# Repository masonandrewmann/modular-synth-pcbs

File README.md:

A collection of PCBs I've designed since getting into DIY modular synths. Do not assume that any of these designs work or are good, many of them have errors I have not fixed yet. If you want to get some manufactured, go ahead but I'd urge you to contact me first and I can let you know any quirks of the board first! :~)

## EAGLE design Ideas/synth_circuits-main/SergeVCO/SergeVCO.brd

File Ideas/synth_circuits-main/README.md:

# synth_circuits
synthesizer circuits

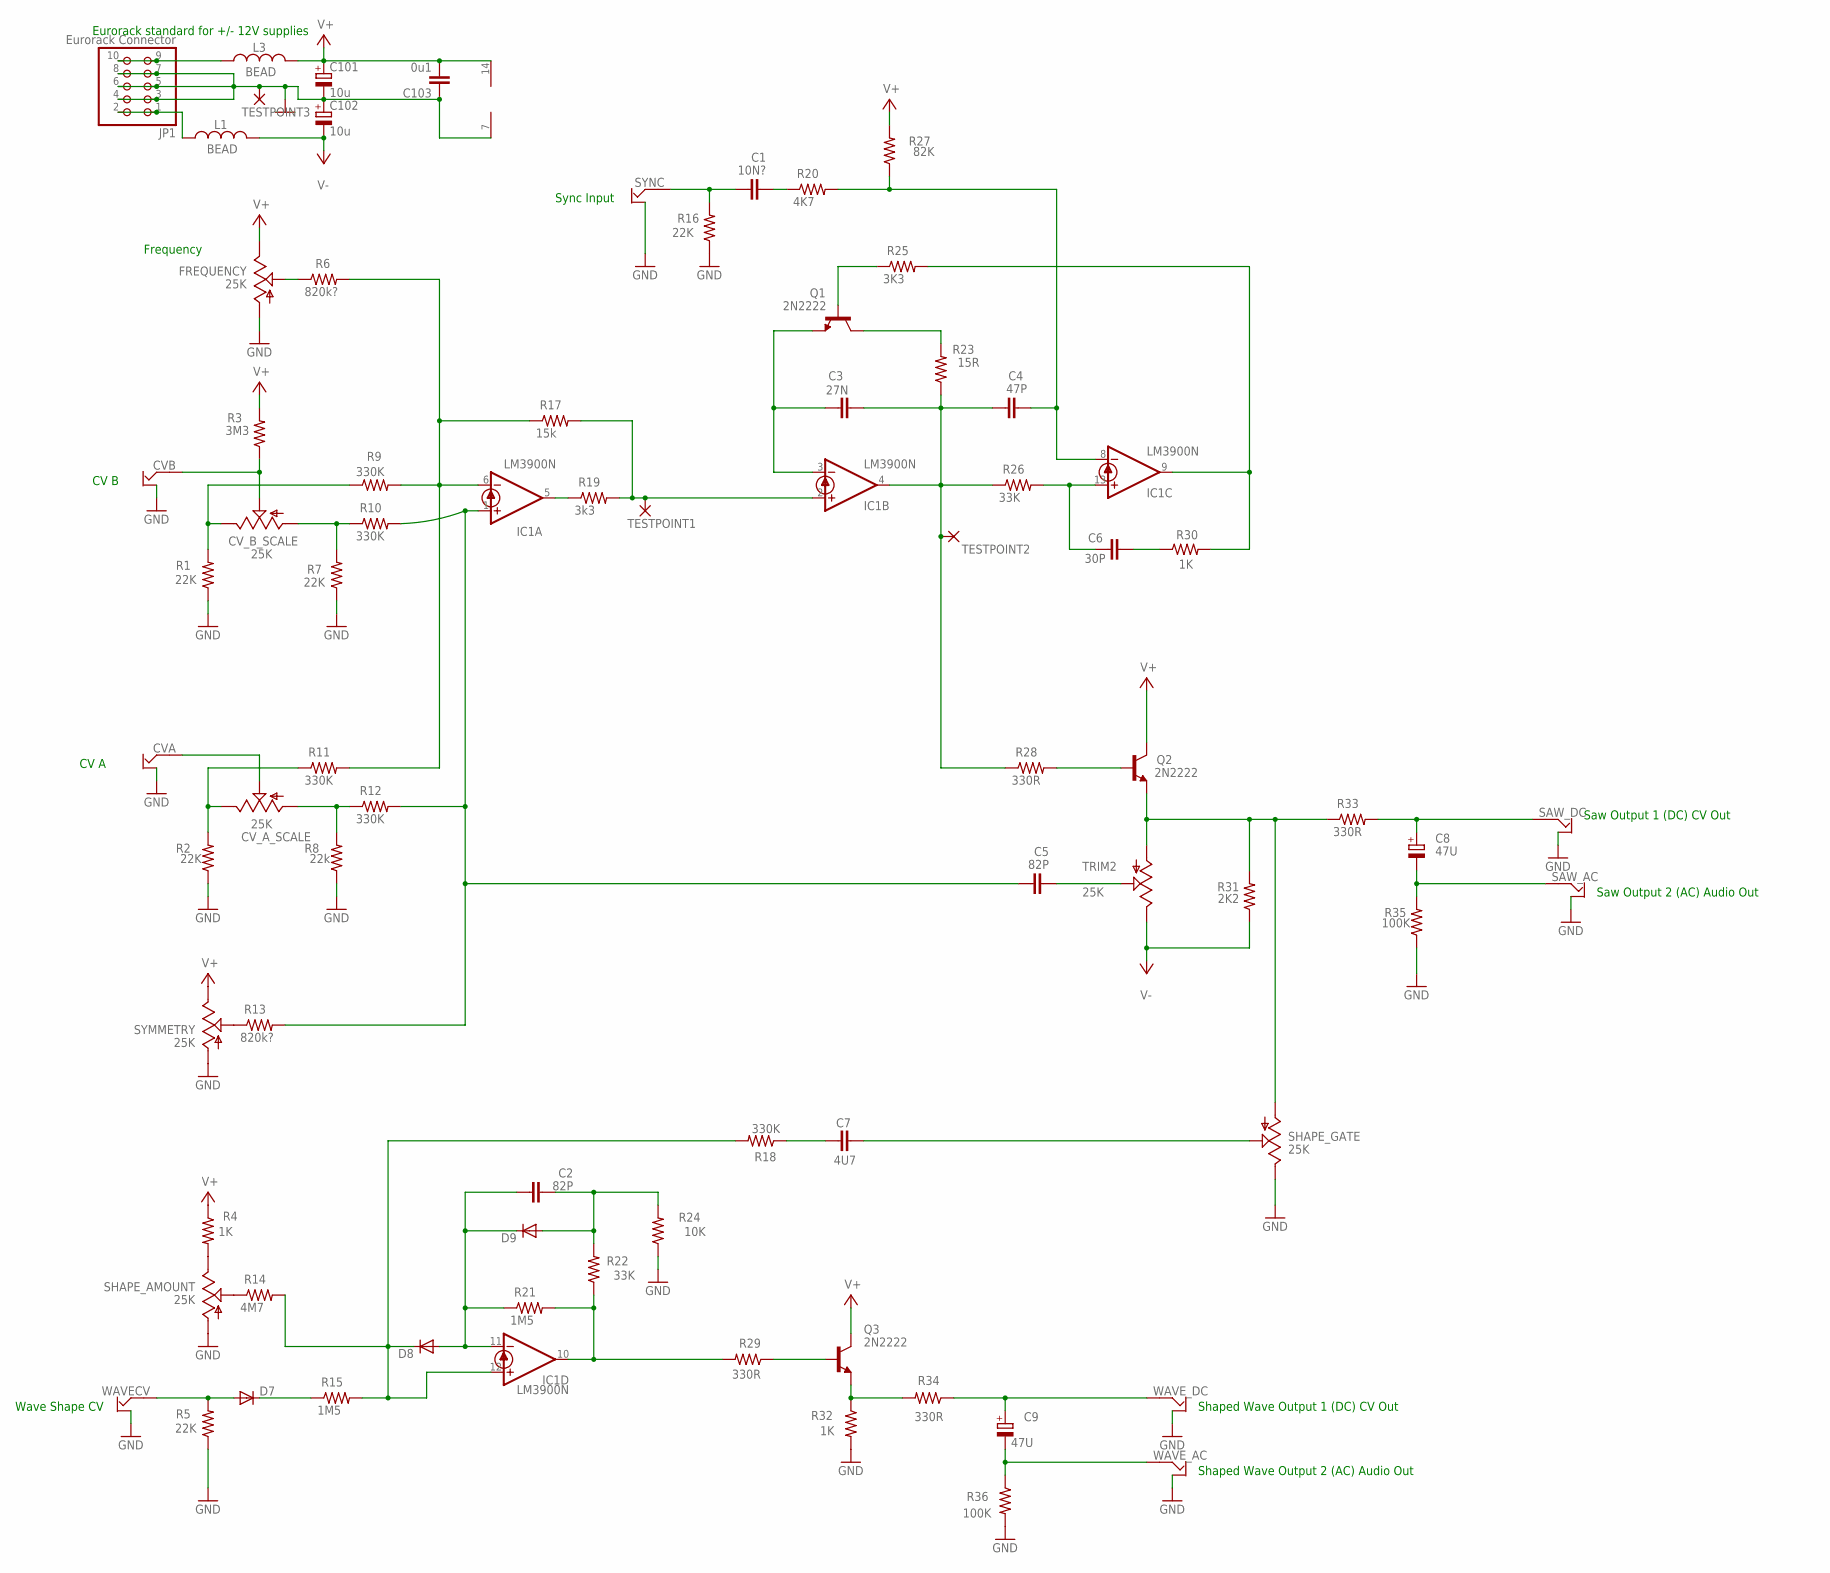
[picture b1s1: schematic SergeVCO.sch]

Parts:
C1: 10N?; C050-025X075-AARON
C2, C5: 82P; C050-025X075-AARON
C3: 27N; C050-025X075-AARON
C4: 47P; C050-025X075-AARON
C6: 30P; C050-025X075-AARON
C7: 4U7; C050-025X075-AARON
C8, C9: 47U; E1,8-4
C101, C102: 10u; E1,8-4
C103: 0u1; C050-025X075-AARON
CVA: OFFBOARD2JACKALT_AARON; OFFBOARD2JACKALT
CVB: OFFBOARD2JACKALT_AARON; OFFBOARD2JACKALT
CV_A_SCALE: 25K; B64Y
CV_B_SCALE: 25K; B64Y
D7, D8, D9: SMALL_DIODEDO35-7; DO35-7
FREQUENCY: 25K; B64Y
IC1: LM3900N; DIL14
JP1: Eurorack Connector; 2X05
L1, L3: BEAD; 0207/10
Q1, Q2, Q3: 2N2222; TO92-EBC-OVAL
R1, R2, R5, R7, R16: 22K; 0207/10
R3: 3M3; 0207/10
R4, R30, R32: 1K; 0207/10
R6, R13: 820k?; 0207/10
R8: 22k; 0207/10
R9, R10, R11, R12, R18: 330K; 0207/10
R14: 4M7; 0207/10
R15, R21: 1M5; 0207/10
R17: 15k; 0207/10
R19: 3k3; 0207/10
R20: 4K7; 0207/10
R22, R26: 33K; 0207/10
R23: 15R; 0207/10
R24: 10K; 0207/10
R25: 3K3; 0207/10
R27: 82K; 0207/10
R28, R29, R33, R34: 330R; 0207/10
R31: 2K2; 0207/10
R35, R36: 100K; 0207/10
SAW_AC: OFFBOARD2JACKALT_AARON; OFFBOARD2JACKALT
SAW_DC: OFFBOARD2JACKALT_AARON; OFFBOARD2JACKALT
SHAPE_AMOUNT: 25K; B64Y
SHAPE_GATE: 25K; B64Y
SYMMETRY: 25K; B64Y
SYNC: OFFBOARD2JACKALT_AARON; OFFBOARD2JACKALT
TESTPOINT1, TESTPOINT2, TESTPOINT3: IOPAD_AARON; ELLIPTICALPADSINGLE
TRIM2: 25K; RS3
WAVECV: OFFBOARD2JACKALT_AARON; OFFBOARD2JACKALT
WAVE_AC: OFFBOARD2JACKALT_AARON; OFFBOARD2JACKALT
WAVE_DC: OFFBOARD2JACKALT_AARON; OFFBOARD2JACKALT

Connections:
GND: C101.-, C102.+, C103.1, CVA.GND, CVB.GND, FREQUENCY.A, IC1.7 (GND), JP1.3, JP1.4, JP1.5, JP1.6, JP1.7, JP1.8, R1.1, R2.1, R5.1, R7.1, R8.1, R16.1, R24.1, R32.2, R35.1, R36.2, SAW_AC.GND, SAW_DC.GND, SHAPE_AMOUNT.A, SHAPE_GATE.E, SYMMETRY.A, SYNC.GND, TESTPOINT3.P$1, WAVECV.GND, WAVE_AC.GND, WAVE_DC.GND
unnamed: FREQUENCY.S, R6.1
unnamed: CVB.SIGNAL, CV_B_SCALE.S, R3.1
unnamed: CV_B_SCALE.E, R1.2, R9.1
unnamed: CV_B_SCALE.A, R7.2, R10.1
unnamed: R13.1, SYMMETRY.S
unnamed: R4.2, SHAPE_AMOUNT.E
unnamed: R14.1, SHAPE_AMOUNT.S
unnamed: D7.A, R5.2, WAVECV.SIGNAL
unnamed: D7.C, R15.1
unnamed: CVA.SIGNAL, CV_A_SCALE.S
unnamed: CV_A_SCALE.E, R2.2, R11.1
unnamed: CV_A_SCALE.A, R8.2, R12.1
unnamed: C5.1, IC1.1 (+IN), R10.2, R12.2, R13.2
unnamed: IC1.6 (-IN), R6.2, R9.2, R11.2, R17.1
unnamed: C3.1, IC1.3 (-IN), Q1.E
unnamed: C2.1, D8.A, D9.C, IC1.11 (-IN), R21.1
unnamed: D8.C, IC1.12 (+IN), R14.2, R15.2, R18.2
unnamed: IC1.10 (OUT), R21.2, R22.1, R29.2
unnamed: C2.2, D9.A, R22.2, R24.2
unnamed: C7.1, R18.1
unnamed: C7.2, SHAPE_GATE.S
unnamed: Q3.B, R29.1
unnamed: Q3.E, R32.1, R34.2
unnamed: C9.-, R36.1, WAVE_AC.SIGNAL
unnamed: C9.+, R34.1, WAVE_DC.SIGNAL
unnamed: IC1.2 (+IN), R17.2, R19.2, TESTPOINT1.P$1
unnamed: IC1.5 (OUT), R19.1
unnamed: C1.1, R16.2, SYNC.SIGNAL
unnamed: C3.2, C4.1, IC1.4 (OUT), R23.1, R26.1, R28.1, TESTPOINT2.P$1
unnamed: C1.2, R20.1
unnamed: Q1.C, R23.2
unnamed: Q1.B, R25.1
unnamed: C6.1, IC1.13 (+IN), R26.2
unnamed: Q2.B, R28.2
unnamed: C4.2, IC1.8 (-IN), R20.2, R27.1
unnamed: C6.2, R30.1
unnamed: IC1.9 (OUT), R25.2, R30.2
unnamed: C8.+, R33.2, SAW_DC.SIGNAL
unnamed: Q2.E, R31.2, R33.1, SHAPE_GATE.A, TRIM2.A
unnamed: C5.2, TRIM2.S
unnamed: C8.-, R35.2, SAW_AC.SIGNAL
unnamed: JP1.1, JP1.2, L1.1
unnamed: JP1.9, JP1.10, L3.1
V+: C101.+, C103.2, FREQUENCY.E, IC1.14 (V+), L3.2, Q2.C, Q3.C, R3.2, R4.1, R27.2, SYMMETRY.E
V-: C102.-, L1.2, R31.1, TRIM2.E

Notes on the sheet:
Eurorack standard for +/- 12V supplies
Frequency
CV B
CV A
Shaped Wave Output 1 (DC) CV Out
Shaped Wave Output 2 (AC) Audio Out
Saw Output 1 (DC) CV Out
Saw Output 2 (AC) Audio Out
Sync Input
Wave Shape CV

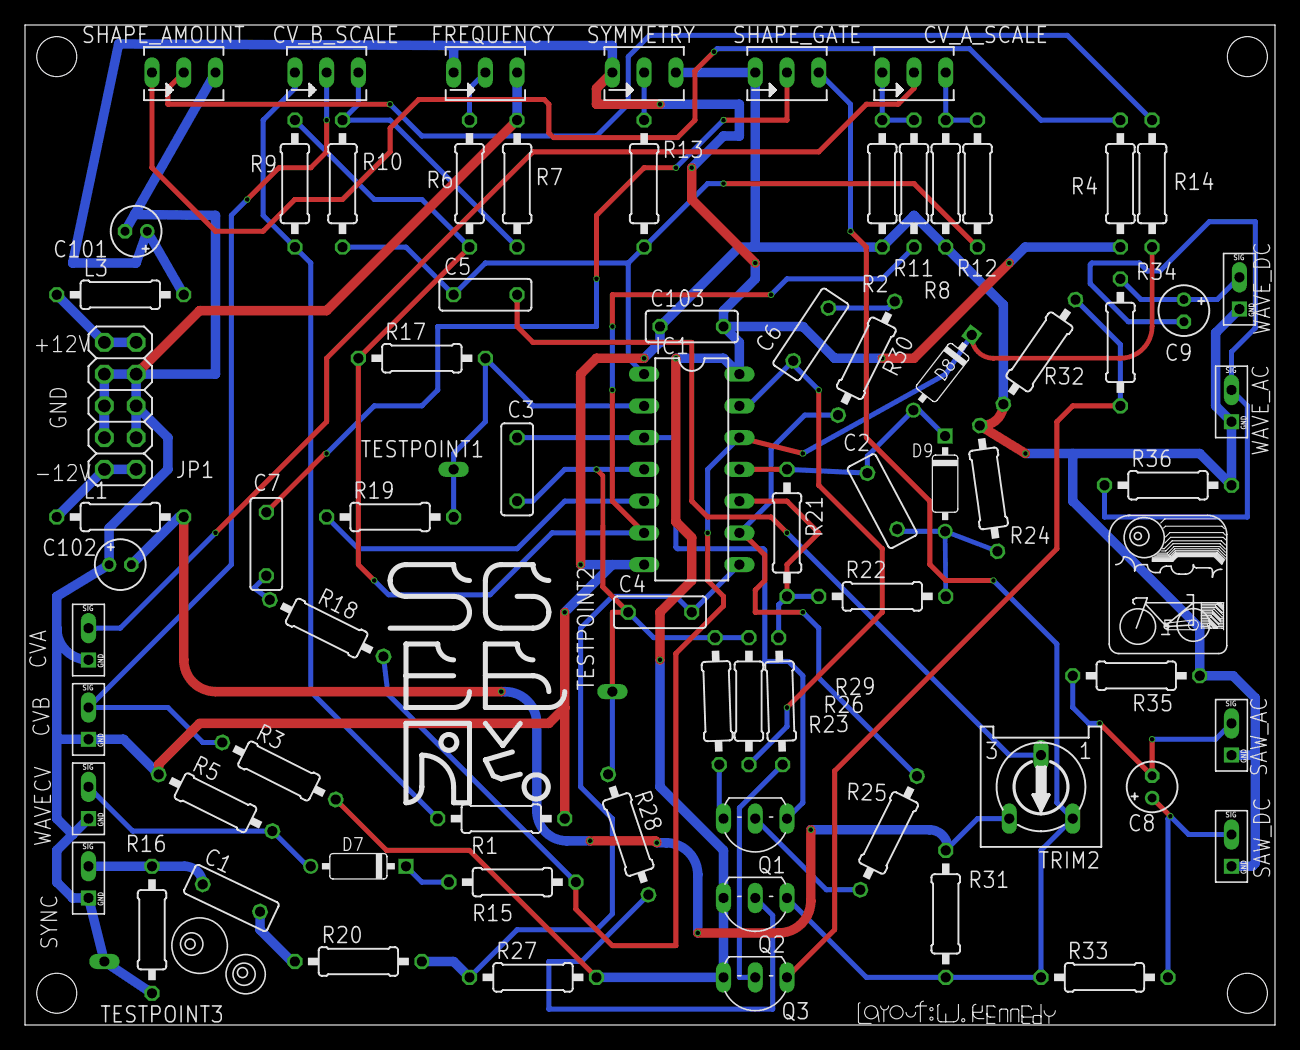
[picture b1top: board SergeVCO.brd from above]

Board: 2 copper layers, 100.0 x 80.0 mm, 76 parts (0 on the bottom side), 46 nets.

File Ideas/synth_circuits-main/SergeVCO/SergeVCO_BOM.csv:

"Qty";"Value";"Device";"Package";"Parts";"Description";"POPULARITY";"SPICEPREFIX";
"3";"";"SMALL_DIODEDO35-7";"DO35-7";"D7, D8, D9";"Small Signal Diode";"";"";
"1";"0u1";"C-EU050-025X075-AARON";"C050-025X075-AARON";"C103";"CAPACITOR, European symbol";"";"";
"2";"100K";"R-US_0207/10";"0207/10";"R35, R36";"RESISTOR, American symbol";"";"";
"1";"10K";"R-US_0207/10";"0207/10";"R24";"RESISTOR, American symbol";"";"";
"1";"10N?";"C-EU050-025X075-AARON";"C050-025X075-AARON";"C1";"CAPACITOR, European symbol";"";"";
"2";"10u";"CPOL-EUE1.8-4";"E1,8-4";"C101, C102";"POLARIZED CAPACITOR, European symbol";"";"";
"1";"15R";"R-US_0207/10";"0207/10";"R23";"RESISTOR, American symbol";"";"";
"1";"15k";"R-US_0207/10";"0207/10";"R17";"RESISTOR, American symbol";"";"";
"3";"1K";"R-US_0207/10";"0207/10";"R4, R30, R32";"RESISTOR, American symbol";"";"";
"2";"1M5";"R-US_0207/10";"0207/10";"R15, R21";"RESISTOR, American symbol";"";"";
"5";"22K";"R-US_0207/10";"0207/10";"R1, R2, R5, R7, R16";"RESISTOR, American symbol";"";"";
"1";"22k";"R-US_0207/10";"0207/10";"R8";"RESISTOR, American symbol";"";"";
"6";"25K";"TRIM_US-B64Y";"B64Y";"CV_A_SCALE, CV_B_SCALE, FREQUENCY, SHAPE_AMOUNT, SHAPE_GATE, SYMMETRY";"POTENTIOMETER";"";"";
"1";"25K";"TRIM_US-RS3";"RS3";"TRIM2";"POTENTIOMETER";"0";"";
"1";"27N";"C-EU050-025X075-AARON";"C050-025X075-AARON";"C3";"CAPACITOR, European symbol";"";"";
"1";"2K2";"R-US_0207/10";"0207/10";"R31";"RESISTOR, American symbol";"";"";
"3";"2N2222";"2N2222";"TO92-EBC-OVAL";"Q1, Q2, Q3";"NPN TRANSISTOR";"";"";
"1";"30P";"C-EU050-025X075-AARON";"C050-025X075-AARON";"C6";"CAPACITOR, European symbol";"";"";
"5";"330K";"R-US_0207/10";"0207/10";"R9, R10, R11, R12, R18";"RESISTOR, American symbol";"";"";
"4";"330R";"R-US_0207/10";"0207/10";"R28, R29, R33, R34";"RESISTOR, American symbol";"";"";
"2";"33K";"R-US_0207/10";"0207/10";"R22, R26";"RESISTOR, American symbol";"";"";
"1";"3K3";"R-US_0207/10";"0207/10";"R25";"RESISTOR, American symbol";"";"";
"1";"3M3";"R-US_0207/10";"0207/10";"R3";"RESISTOR, American symbol";"";"";
"1";"3k3";"R-US_0207/10";"0207/10";"R19";"RESISTOR, American symbol";"";"";
"1";"47P";"C-EU050-025X075-AARON";"C050-025X075-AARON";"C4";"CAPACITOR, European symbol";"";"";
"2";"47U";"CPOL-EUE1.8-4";"E1,8-4";"C8, C9";"POLARIZED CAPACITOR, European symbol";"";"";
"1";"4K7";"R-US_0207/10";"0207/10";"R20";"RESISTOR, American symbol";"";"";
"1";"4M7";"R-US_0207/10";"0207/10";"R14";"RESISTOR, American symbol";"";"";
"1";"4U7";"C-EU050-025X075-AARON";"C050-025X075-AARON";"C7";"CAPACITOR, European symbol";"";"";
"2";"820k?";"R-US_0207/10";"0207/10";"R6, R13";"RESISTOR, American symbol";"";"";
"1";"82K";"R-US_0207/10";"0207/10";"R27";"RESISTOR, American symbol";"";"";
"2";"82P";"C-EU050-025X075-AARON";"C050-025X075-AARON";"C2, C5";"CAPACITOR, European symbol";"";"";
"2";"BEAD";"L-US0207/10";"0207/10";"L1, L3";"INDUCTOR, American symbol";"6";"L";
"1";"Eurorack Connector";"PINHD-2X5";"2X05";"JP1";"PIN HEADER";"35";"";
"3";"IOPAD_AARON";"IOPAD_AARON";"ELLIPTICALPADSINGLE";"TESTPOINT1, TESTPOINT2, TESTPOINT3";"";"";"";
"1";"LM3900N";"LM3900N";"DIL14";"IC1";"OP AMP";"0";"";
"8";"OFFBOARD2JACKALT_AARON";"OFFBOARD2JACKALT_AARON";"OFFBOARD2JACKALT";"CVA, CVB, SAW_AC, SAW_DC, SYNC, WAVECV, WAVE_AC, WAVE_DC";"";"";"";

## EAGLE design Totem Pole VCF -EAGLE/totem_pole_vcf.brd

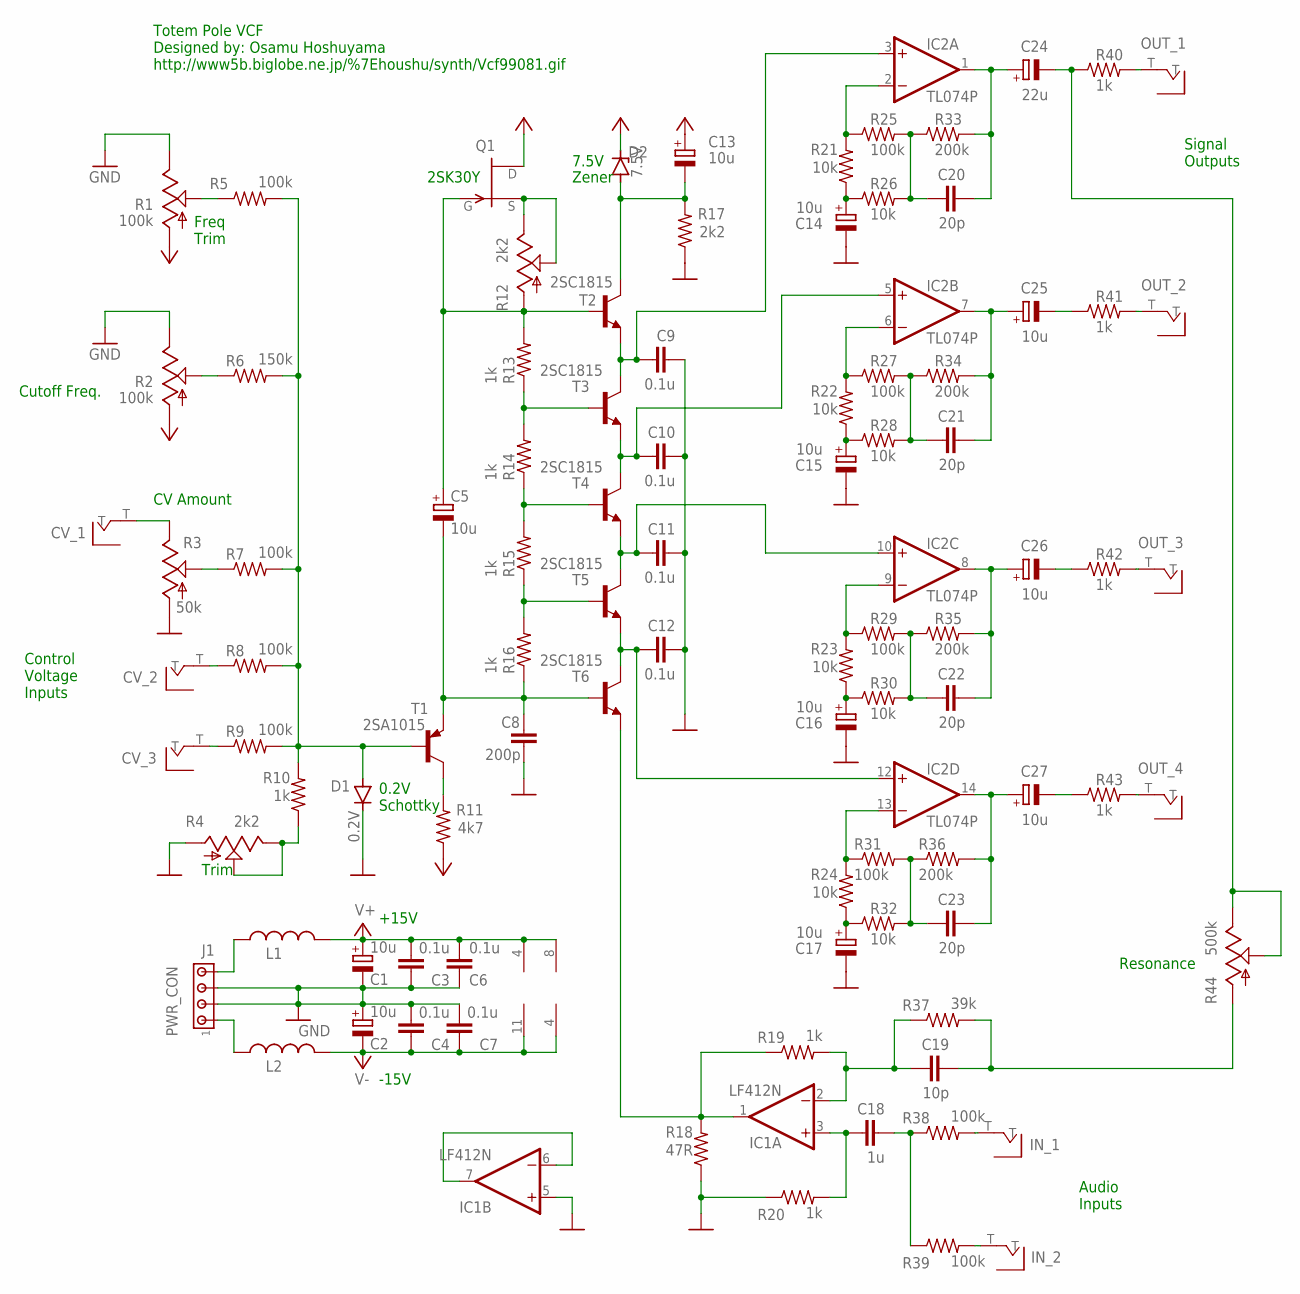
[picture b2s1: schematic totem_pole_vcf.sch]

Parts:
C1, C2, C5, C13, C14, C15, C16, C17, C25, C26, C27: 10u; E1,8-4
C3, C4, C6, C7, C9, C10, C11, C12: 0.1u; C050-025X075
C8: 200p; C050-025X075
C18: 1u; C050-025X075
C19: 10p; C050-025X075
C20, C21, C22, C23: 20p; C050-025X075
C24: 22u; E1,8-4
CV_1, CV_2, CV_3: OFFBOARD_JACK
D1: 0.2V; D-10
D2: 7.5V; DO41Z10
IC1: LF412N; DIL08
IC2: TL074P; DIL14
IN_1, IN_2: OFFBOARD_JACK
J1: PWR_CON; 1X4MTA
L1, L2: BEAD; 0207/10
OUT_1, OUT_2, OUT_3, OUT_4: OFFBOARD_JACK
Q1: 2N3819; TO92
R1: 100k; RS3
R2: 100k; B64Y
R3: 50k; B64Y
R4, R12: 2k2; RS3
R5, R7, R8, R9, R25, R27, R29, R31, R38, R39: 100k; 0207/10
R6: 150k; 0207/10
R10, R13, R14, R15, R16, R19, R20, R40, R41, R42, R43: 1k; 0207/10
R11: 4k7; 0207/10
R17: 2k2; 0207/10
R18: 47R; 0207/10
R21, R22, R23, R24, R26, R28, R30, R32: 10k; 0207/10
R33, R34, R35, R36: 200k; 0207/10
R37: 39k; 0207/10
R44: 500k; RS3
T1: 2SA1015; TO92
T2, T3, T4, T5, T6: 2SC1815; TO92-ECB

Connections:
GND: C1.-, C2.+, C3.2, C4.1, C6.1, C7.1, C8.1, C9.2, C10.2, C11.2, C12.2, C14.-, C15.-, C16.-, C17.-, D1.C, IC1.5 (+IN), J1.2, J1.3, R1.E, R2.E, R3.A, R4.A, R17.1, R18.1, R20.1
unnamed: D1.A, R5.2, R6.2, R7.2, R8.2, R9.2, R10.2, T1.2 (B)
unnamed: C5.-, C8.2, R16.1, T1.1 (E), T6.B
unnamed: C12.1, IC2.12 (+IN), T5.E, T6.C
unnamed: R15.1, R16.2, T5.B
unnamed: R14.1, R15.2, T4.B
unnamed: R13.1, R14.2, T3.B
unnamed: OUT_1.T, R40.2
unnamed: C11.1, IC2.10 (+IN), T4.E, T5.C
unnamed: C9.1, IC2.3 (+IN), T2.E, T3.C
unnamed: C5.+, Q1.2 (G), R12.A, R13.2, T2.B
unnamed: IC2.2 (-IN), R21.2, R25.1
unnamed: Q1.3 (S), R12.E, R12.S
unnamed: C14.+, R21.1, R26.1
unnamed: C20.1, R25.2, R26.2, R33.1
unnamed: C20.2, C24.+, IC2.1 (OUT), R33.2
unnamed: C13.-, D2.A, R17.2, T2.C
unnamed: C18.1, IC1.3 (+IN), R20.2
unnamed: C18.2, R38.1, R39.1
unnamed: IC1.1 (OUT), R18.2, R19.1, T6.E
unnamed: IC2.6 (-IN), R22.2, R27.1
unnamed: C19.1, IC1.2 (-IN), R19.2, R37.1
unnamed: C19.2, R37.2, R44.A
unnamed: C15.+, R22.1, R28.1
unnamed: C21.1, R27.2, R28.2, R34.1
unnamed: C21.2, C25.+, IC2.7 (OUT), R34.2
unnamed: C25.-, R41.1
unnamed: IC2.9 (-IN), R23.2, R29.1
unnamed: C16.+, R23.1, R30.1
unnamed: C22.1, R29.2, R30.2, R35.1
unnamed: C22.2, C26.+, IC2.8 (OUT), R35.2
unnamed: C26.-, R42.1
unnamed: IC2.13 (-IN), R24.2, R31.1
unnamed: C17.+, R24.1, R32.1
unnamed: C23.1, R31.2, R32.2, R36.1
unnamed: C23.2, C27.+, IC2.14 (OUT), R36.2
unnamed: C27.-, R43.1
unnamed: IC1.6 (-IN), IC1.7 (OUT)
unnamed: R3.S, R7.1
unnamed: R4.E, R4.S, R10.1
unnamed: J1.1, L2.1
unnamed: J1.4, L1.1
unnamed: C10.1, IC2.5 (+IN), T3.E, T4.C
unnamed: R2.S, R6.1
unnamed: R1.S, R5.1
unnamed: R11.2, T1.3 (C)
unnamed: CV_1.T, R3.E
unnamed: OUT_2.T, R41.2
unnamed: CV_2.T, R8.1
unnamed: CV_3.T, R9.1
unnamed: OUT_3.T, R42.2
unnamed: OUT_4.T, R43.2
unnamed: IN_1.T, R38.2
unnamed: IN_2.T, R39.2
unnamed: C24.-, R40.1, R44.E, R44.S
V+: C1.+, C3.1, C6.2, C13.+, D2.C, IC1.8 (V+), IC2.4 (V+), L1.2, Q1.1 (D)
V-: C2.-, C4.2, C7.2, IC1.4 (V-), IC2.11 (V-), L2.2, R1.A, R2.A, R11.1

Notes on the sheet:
Cutoff Freq.
Trim
CV Amount
0.2V Schottky
7.5V
Zener
2SK30Y
Resonance
+15V
-15V
Totem Pole VCF Designed by: Osamu Hoshuyama http://www5b.biglobe.ne.jp/%7Ehoushu/synth/Vcf99081.gif
Control Voltage Inputs
Signal Outputs
Audio Inputs
Freq Trim

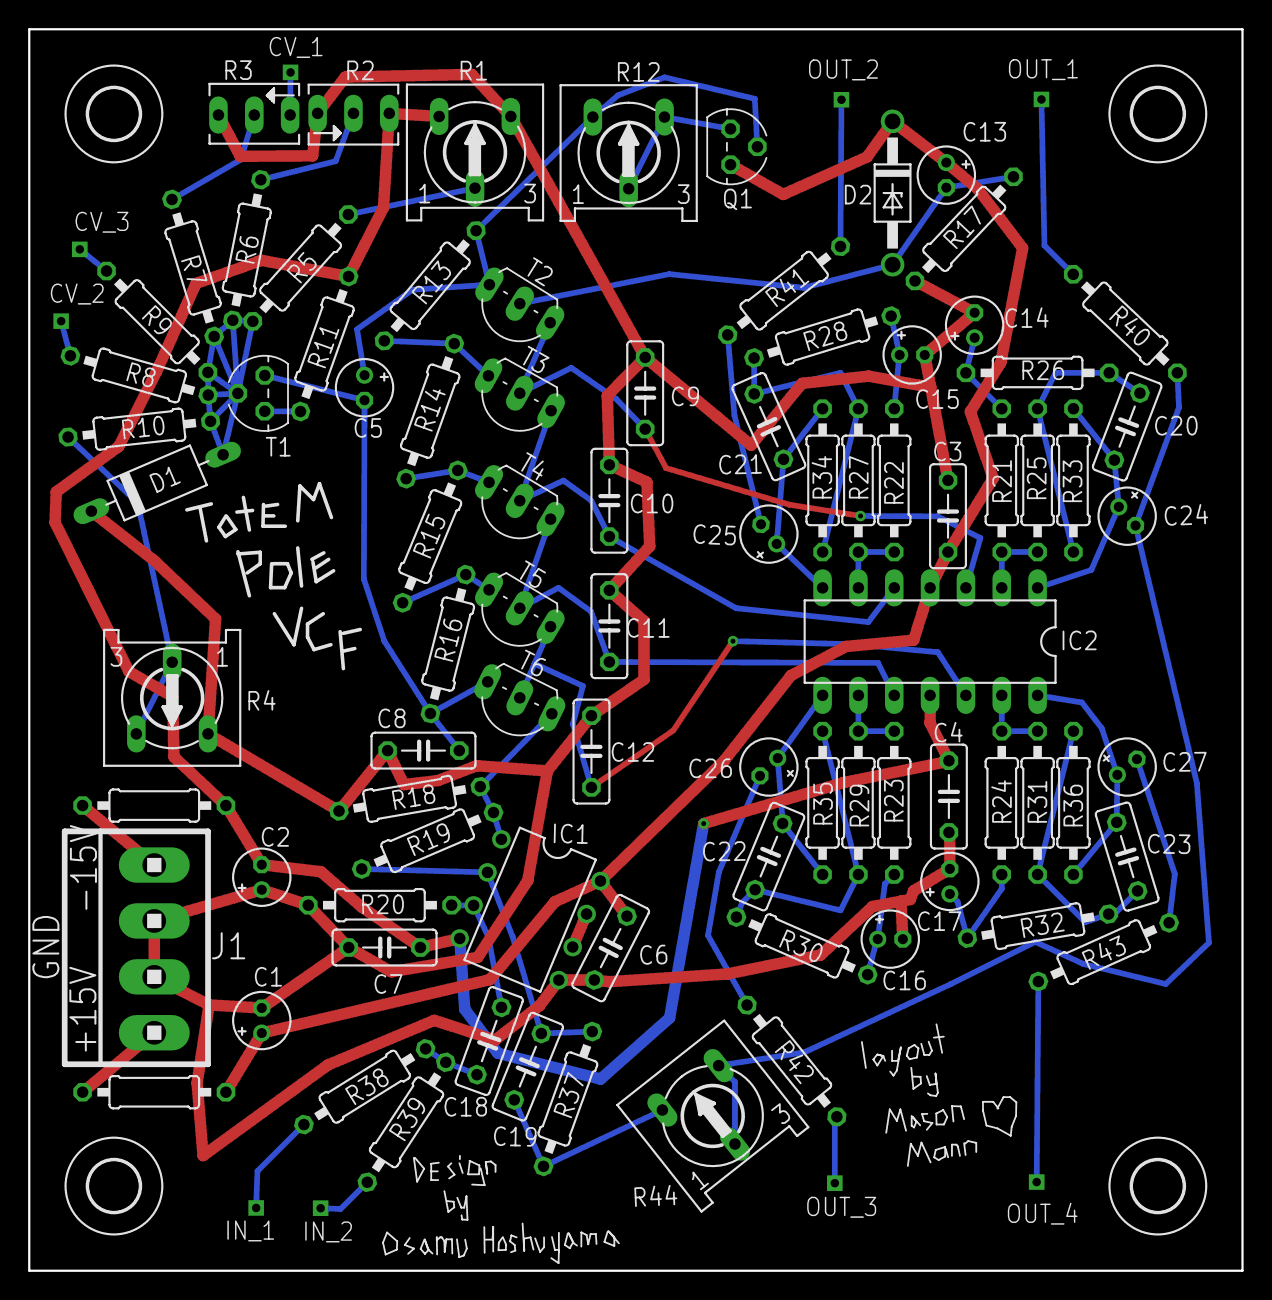
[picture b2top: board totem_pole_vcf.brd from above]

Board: 2 copper layers, 86.0 x 88.0 mm, 98 parts (0 on the bottom side), 57 nets.

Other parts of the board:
U$1, U$2, U$3, U$4: 3,6

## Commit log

2020-12-14 hiiii
2020-12-14 wow pcbs
2021-01-03 whoops
2021-01-03 added component list and datasheets uwu
2021-01-03 datasheets for 2N3906 and 2N3904 added
2021-01-03 replaced bad datasheets
2021-01-04 more sheetzp-0o
2021-01-04 finished schematic, placed and arranged parts on pcbnew
2021-01-04 fixed some incorrect component values
2021-01-04 pcb design for VCA finished
2021-01-05 fixed a schematic error with transistor pinout. pcb not updated yet
2021-01-05 fixed transistor pinout on pcb
2021-01-05 added ground fills and vias to shorten ground paths
2021-01-05 fixed a bad via and exported gerber and drl files
2021-01-05 silkscreen cleanup
2021-01-05 cleaned up pcb, fixed bridge rectifier pinout, added silkscreen and exported fabrication files
2021-01-05 added BOM file
2021-01-07 added design rule screenshots
2021-01-11 checked over schematic and added footprints for all but capacitors
2021-01-11 assigned footprints
2021-01-11 layout passes drc
2021-01-11 silkscreen designators placed
2021-01-11 doodled on silkscreen
2021-01-13 checked schematic and assigned footprints
2021-01-13 placed components in general location on pcb uwu
2021-01-17 VCF PCB
2021-01-17 hi i miight have done smth i dont remember uwu
2021-01-24 idk maybe i changed smth
2021-01-24 added functional silkscreen
2021-01-24 fixed error on silkscreen (input/output labels)
2021-01-24 made silkscreen pretty
2021-01-25 vcf done
2021-01-25 hiiiii
2021-01-29 added schematic for VC reverb
2021-01-30 placed components on pcb, some caps i think have the wrong footprint
2021-01-30 progress on wiring
2021-02-01 finished back copper connections
2021-03-07 probably changed some stuff idk
2021-04-04 added serge USG
2021-04-04 added power connectors to DUSG
2021-04-04 DUSG fabrication outputs added
2021-04-05 DUSG updates
2021-04-12 datasheets and BOM
2021-05-08 lots of stuff tbh
2021-05-08 fixed error and rerouted VCO
2021-05-09 finished sequencer schematic
2021-05-09 checked over sequencer schematic
2021-05-09 VCO - added tempco resistor holes
2021-05-09 added totem pole VCF
2021-05-09 fixed eagle gerbers
2021-05-12 sequencer pcb designed and base silkscreen
2021-05-12 hiii
2021-05-12 added micro sample hold schematic
2021-05-12 triple waveshaper schematic added
2021-05-12 added noise cornu schematic
2021-05-12 added triple waveshaper pcb
2021-05-12 sample hold pcb added
2021-05-12 pwr connector silkscreen
2021-05-12 added noise pcb
2021-05-13 made silkscreens pretty
2021-05-13 beep
2021-05-18 front panel work
2021-05-19 Finished ambisonics schematics
2021-05-19 moved samplehold file
2021-05-20 ambisonic pcbsdoneee
2021-05-21 finished/plotted ambisonic PCBs
2021-05-26 added more panel desiigns
2021-05-30 added some new boards
2021-05-30 cleaned up silkscreen
2021-05-30 ssg work
2021-05-30 cleaned up ssg silkscreen
2021-05-30 cleaned up voltage quantizer silkscreen
2021-07-18 literally so much stuff
2021-09-21 ooh some new pcbs yayy
2021-09-21 testing token
